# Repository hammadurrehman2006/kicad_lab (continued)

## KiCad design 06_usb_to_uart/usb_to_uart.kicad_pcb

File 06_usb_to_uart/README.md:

# Day 5 – USB to UART Converter (CP2102)

This is **Day 5** of my **10-Day PCB Design Challenge**.
After getting delayed due to heavy rain 🌧️ on 19th Aug, I’m back with my next project – a **USB to UART Converter PCB** designed using **KiCad**.

This project is special because it’s my **first SMD-based PCB design** 🎉 and also introduces **vias** and **ESD protection** for improved reliability.

---

## 📜 Project Overview

The circuit is based on the **CP2102 USB-to-UART Bridge Controller**, which enables easy communication between a computer’s USB port and microcontrollers or other UART-based devices.

### Key Features:

* **USB Type-C input**
* **CP2102 IC (SMD package)**
* **ESD protection diodes** → *LESD5D5.0CT1G*
* **LED indicators** for Power, TX, and RX
* **Decoupling capacitors** for noise reduction
* **External pins** (VCC, GND, TX, RX, RST) for easy interfacing
* **Vias** for better routing on the 2-layer PCB

---

## 🛠 Tools Used

* **KiCad** → Schematic & PCB Design
* **GitHub** → Version control & documentation

---

## 📂 Files in This Project

* **Schematic & PCB files** (KiCad project)
* **Gerber files** (for fabrication)
* **Drill files**
* **Images** (schematic, PCB layout, 3D preview)

---

## 📸 Project Images

### Schematic

### PCB Layout

### 3D PCB Preview

### 3D PCB without components Preview

---

## 📬 Repository Info

* **Folder Name:** `06_usb_to_uart`
* **Author:** Muhammad Hammad ur Rehman
* **License:** Open for learning & educational purposes

---

⚡ This project marks a milestone for me as I move from **through-hole designs** to **SMD-based PCBs** while also learning to use **vias** and **protection circuits** in real-world designs.

---

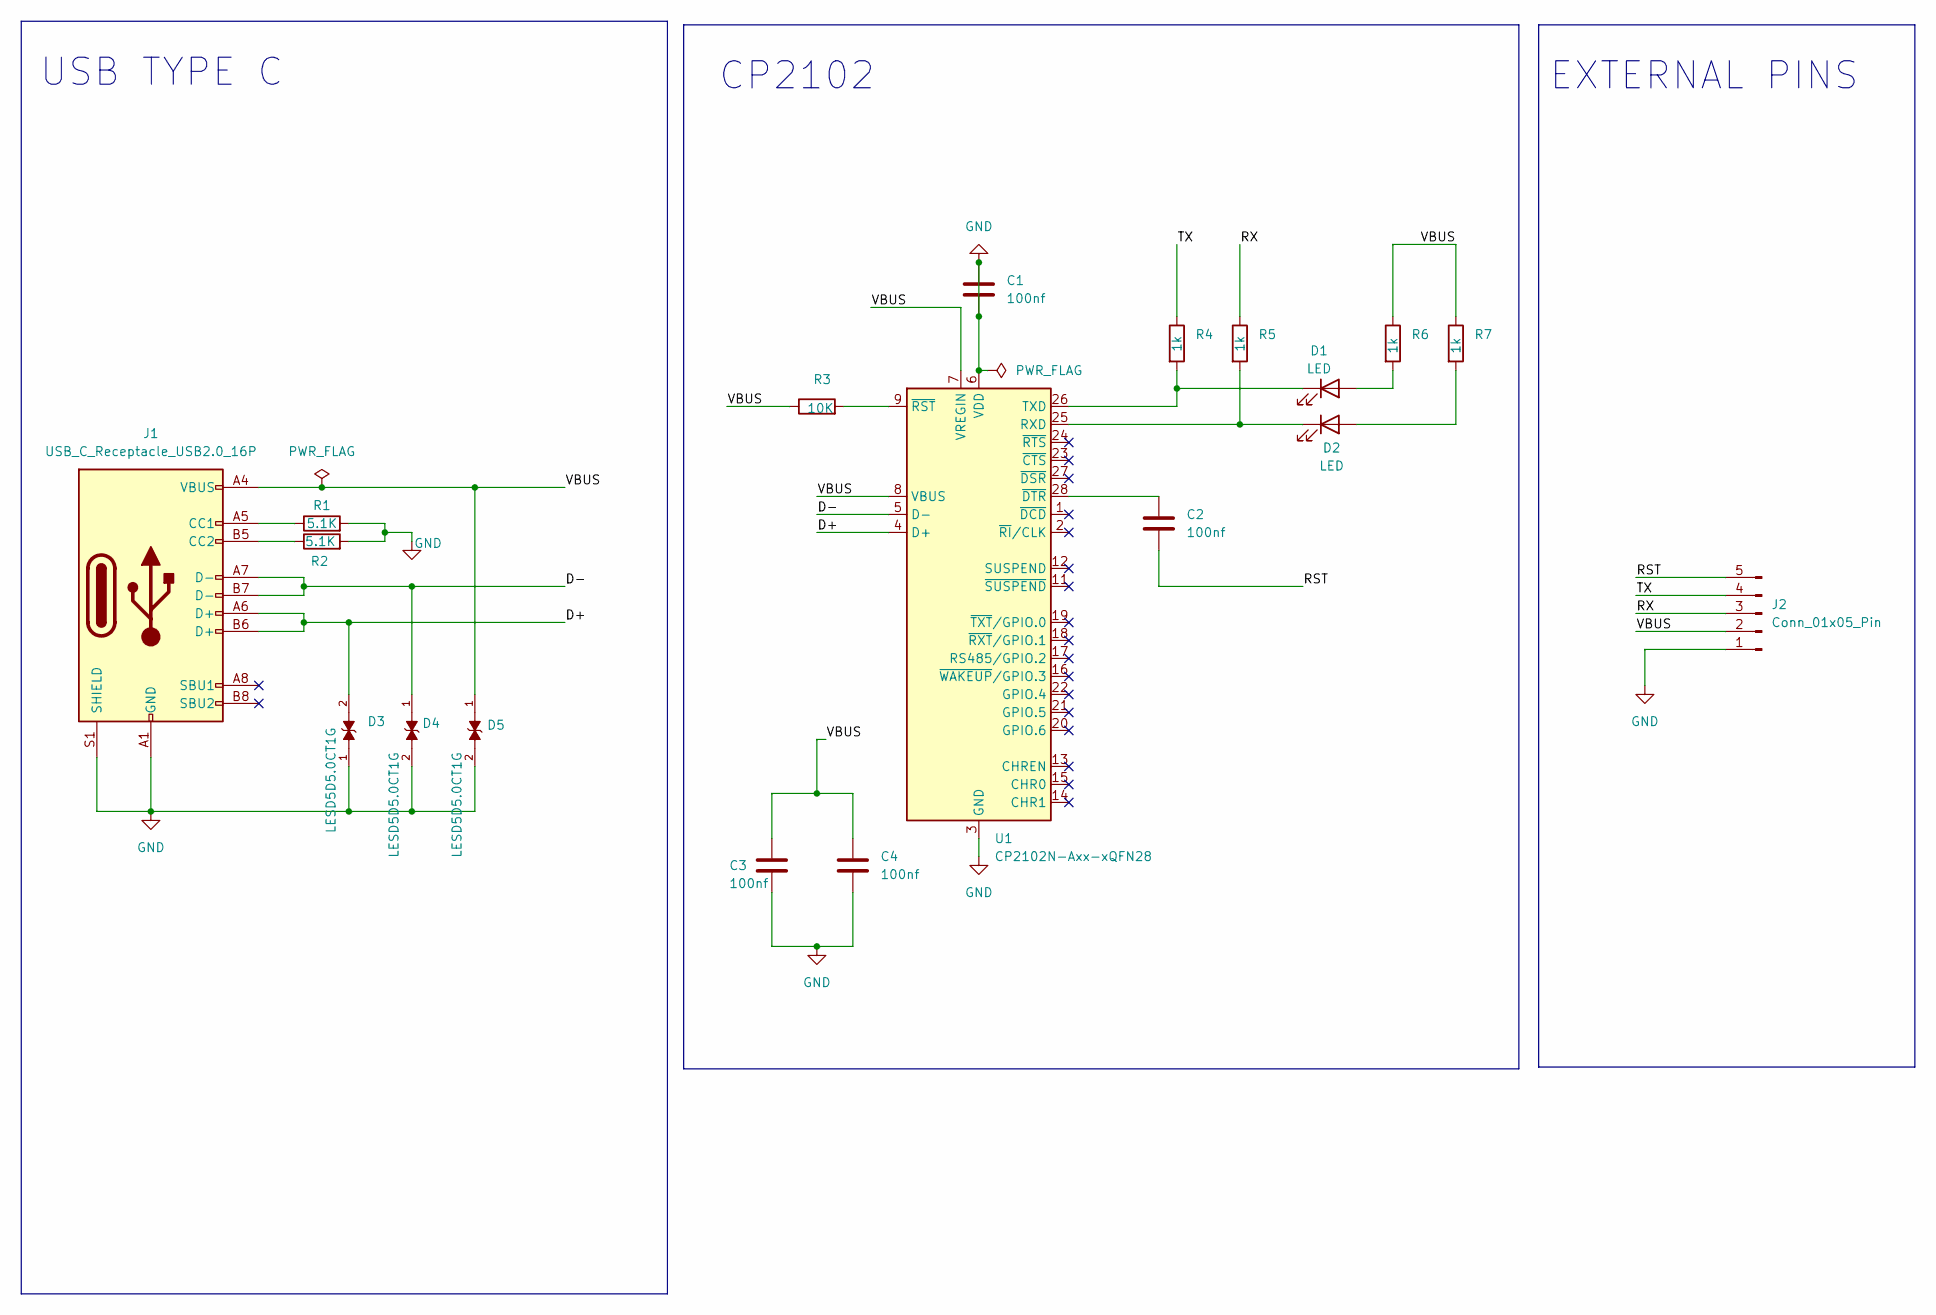
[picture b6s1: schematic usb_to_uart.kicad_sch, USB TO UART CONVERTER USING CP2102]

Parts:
C1, C2, C3, C4: 100nf; C_0201_0603Metric
D1, D2: LED; LED_0201_0603Metric
D3, D4, D5: LESD5D5.0CT1G; TVS_LESD5D5.0CT1G; PARTREV O
J1: USB_C_Receptacle_USB2.0_16P; USB_C_Receptacle_HRO_TYPE-C-31-M-12
J2: Conn_01x05_Pin; PinHeader_1x05_P2.54mm_Horizontal
R1, R2: 5.1K; R_0201_0603Metric
R3: 10K; R_0201_0603Metric
R4, R5, R6, R7: 1k; R_0201_0603Metric
U1: CP2102N-Axx-xQFN28; QFN-28-1EP_5x5mm_P0.5mm_EP3.35x3.35mm

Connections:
/D+: D3.2, J1.A6 (D+), J1.B6 (D+), U1.4 (D+)
/D-: D4.1, J1.A7 (D-), J1.B7 (D-), U1.5 (D-)
/RST: C2.2, J2.5
/RX: J2.3, R5.1
/TX: J2.4, R4.1
/VBUS: C3.1, C4.1, D5.1, J1.A4 (VBUS), J1.A9 (VBUS), J1.B4 (VBUS), J1.B9 (VBUS), J2.2, R3.1, R6.1, R7.1, U1.7 (VREGIN), U1.8 (VBUS)
GND: C1.1, C1.2, C3.2, C4.2, D3.1, D4.2, D5.2, J1.A1 (GND), J1.A12 (GND), J1.B1 (GND), J1.B12 (GND), J1.S1 (SHIELD), J2.1, R1.2, R2.2, U1.3 (GND), U1.6 (VDD), U1.29 (GND)
unnamed: D1.2 (A), R6.2
unnamed: D1.1 (K), R4.2, U1.26 (TXD)
unnamed: D2.2 (A), R7.2
unnamed: D2.1 (K), R5.2, U1.25 (RXD)
unnamed: J1.A5 (CC1), R1.1
unnamed: J1.B5 (CC2), R2.1
unnamed: C2.1, U1.28 (~DTR)
unnamed: R3.2, U1.9 (~RST)

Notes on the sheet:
CP2102
USB TYPE C
EXTERNAL PINS

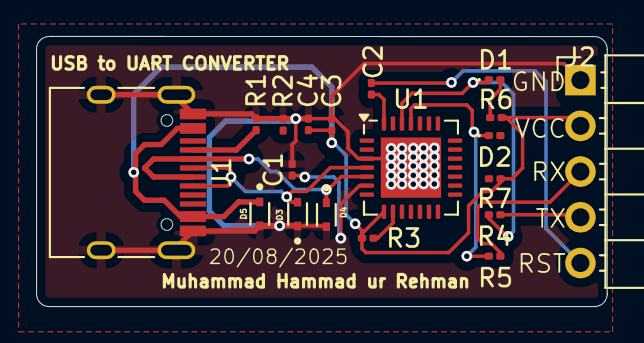
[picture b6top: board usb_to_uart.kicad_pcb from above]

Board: 2 copper layers, 31.7 x 15.0 mm, 19 parts (0 on the bottom side), 15 nets.

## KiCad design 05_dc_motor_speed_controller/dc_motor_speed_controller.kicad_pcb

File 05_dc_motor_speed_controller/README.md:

# Day 4 – DC Motor Speed Controller (PCB Design)

This is **Day 4** of my **10-Day PCB Design Challenge**.  
For today’s project, I designed a **DC Motor Speed Controller PCB** using **KiCad**.  
The circuit is based on a **555 Timer IC** in astable mode, generating PWM to control motor speed via a transistor.

---

## 📜 Project Overview
The circuit includes:
- **1 × Potentiometer** (for speed adjustment)  
- **1 × 555 Timer IC**  
- **2 × Capacitors**  
- **3 × Resistors**  
- **1 × Power Transistor (Q1)**  
- **3 × Diodes**  
- **1 × LED** (status indicator)  
- **2 × 2-Pin Screw Terminals** (power in, motor out)

---

## 🛠 Tools Used
- **KiCad** for schematic and PCB layout  
- **GitHub** for version control  

---

## 📂 Files in This Project
- **Schematic & PCB files** (KiCad project)  
- **Gerber files** for fabrication  
- **Drill files** (included inside Gerbers folder)  
- **Images** for quick preview in this README  

---

## 📸 Project Images

### Schematic

### PCB Layout

### PCB with Components

### PCB Board

---

## 📬 Repository Info
- **Folder Name:** `05_dc_motor_speed_controller`  
- **Author:** Muhammad Hammad ur Rehman  
- **License:** Open for learning and educational purposes  

---

## 🔗 Connect with Me
[LinkedIn](https://www.linkedin.com/in/mhammadurrehman) • [GitHub](https://github.com/hammadurrehman2006)

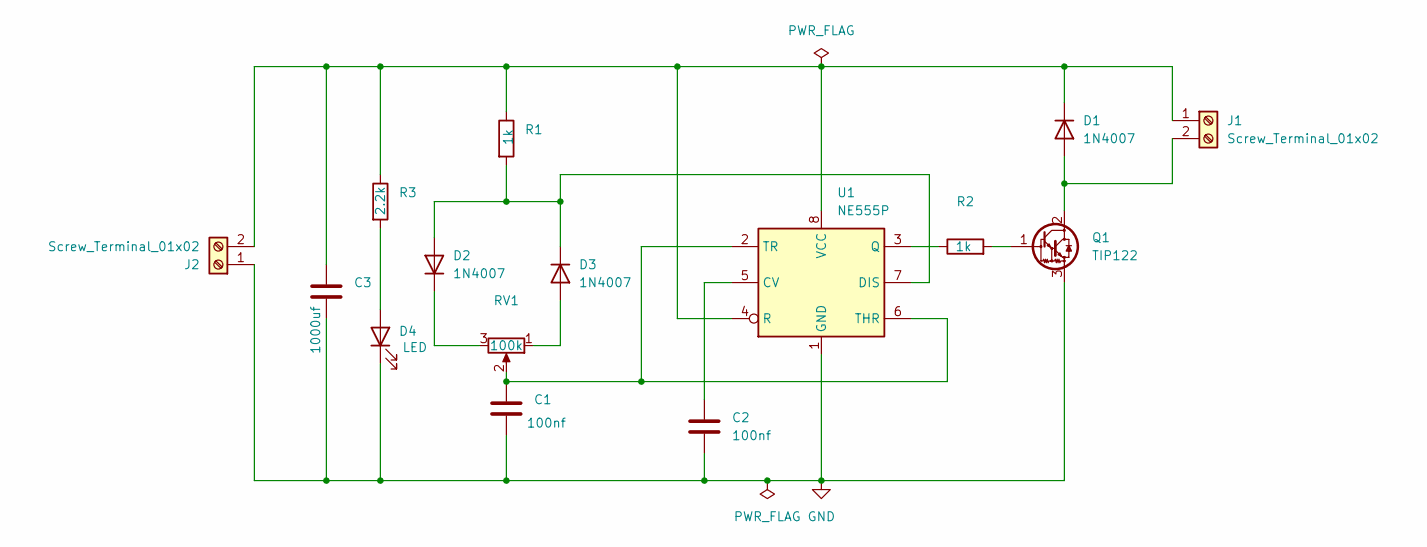
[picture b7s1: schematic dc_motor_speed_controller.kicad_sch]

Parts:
C1, C2: 100nf; C_Disc_D4.7mm_W2.5mm_P5.00mm
C3: 1000uf; CP_Radial_D10.0mm_P5.00mm
D1, D2, D3: 1N4007; D_DO-41_SOD81_P10.16mm_Horizontal
D4: LED; LED_D5.0mm
J1, J2: Screw_Terminal_01x02; TerminalBlock_bornier-2_P5.08mm
Q1: TIP122; TO-220-3_Vertical
R1, R2: 1k; R_Axial_DIN0204_L3.6mm_D1.6mm_P7.62mm_Horizontal
R3: 2.2k; R_Axial_DIN0204_L3.6mm_D1.6mm_P7.62mm_Horizontal
RV1: 100k; Potentiometer_Alps_RK163_Single_Horizontal
U1: NE555P; DIP-8_W7.62mm

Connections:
GND: C1.2, C2.2, C3.2, D4.1 (K), J2.1, Q1.3 (E), U1.1 (GND)
unnamed: D1.2 (A), J1.2, Q1.2 (C)
unnamed: C3.1, D1.1 (K), J1.1, J2.2, R1.1, R3.1, U1.4 (R), U1.8 (VCC)
unnamed: D2.2 (A), D3.1 (K), R1.2, U1.7 (DIS)
unnamed: D2.1 (K), RV1.3
unnamed: D3.2 (A), RV1.1
unnamed: D4.2 (A), R3.2
unnamed: Q1.1 (B), R2.2
unnamed: C2.1, U1.5 (CV)
unnamed: R2.1, U1.3 (Q)
unnamed: C1.1, RV1.2, U1.2 (TR), U1.6 (THR)

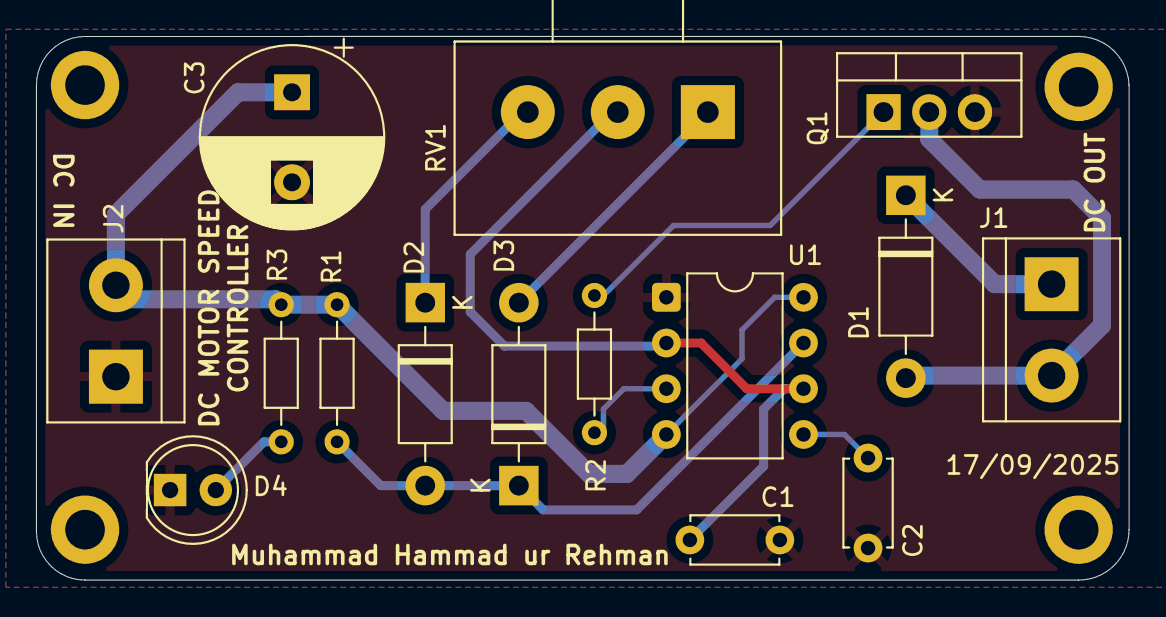
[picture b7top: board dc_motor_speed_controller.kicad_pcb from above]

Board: 2 copper layers, 60.7 x 30.2 mm, 15 parts (0 on the bottom side), 11 nets.

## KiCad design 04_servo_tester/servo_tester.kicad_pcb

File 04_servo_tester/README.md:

# Day 3 – Servo Tester (PCB Design)

This is **Day 3** of my **10-Day PCB Design Challenge**, where I design PCB projects starting from simple circuits and gradually moving towards more complex ones.

For today’s design, I created a **2-layer Servo Tester PCB** using **KiCad**.  
This circuit is based on a **555 Timer IC** and a potentiometer to generate PWM signals for testing servo motors.

---

## 📜 Project Overview
The circuit includes:
- **1 × Potentiometer**  
- **1 × 555 Timer IC**  
- **1 × Capacitor**  
- **3 × Resistors**  
- **1 × Diode**  
- **1 × LED**  
- **1 × 2-Pin Connector**  
- **1 × 3-Pin Connector**  

---

## 🛠 Tools Used
- **KiCad** for schematic and PCB layout  
- **GitHub** for version control  

---

## 📂 Files in This Project
- **`schematic.png`** – Circuit schematic  
- **`board.png`** – PCB front view  
- **`boardC.png`** – PCB with components  
- **`layout.png`** – PCB layout view  

---

## 📸 Project Images

### Schematic

### PCB Board

### PCB with Components

### Layout

---

## 📅 Challenge Context
This project is part of my **10-Day PCB Design Challenge**:
- **Day 1:** AC to DC Converter (Single Layer PCB)  
- **Day 2:** Transformerless Power Supply (2-Layer PCB)  
- **Day 3:** Servo Tester (2-Layer PCB with 555 Timer)  

---

## 📬 Repository Info
- **Folder Name:** `04_servo_tester`  
- **Author:** Muhammad Hammad ur Rehman  
- **License:** Open for learning and educational purposes  

---

## 🔗 Connect with Me
[LinkedIn](https://www.linkedin.com/in/mhammadurrehman) • [GitHub](https://github.com/hammadurrehman2006)

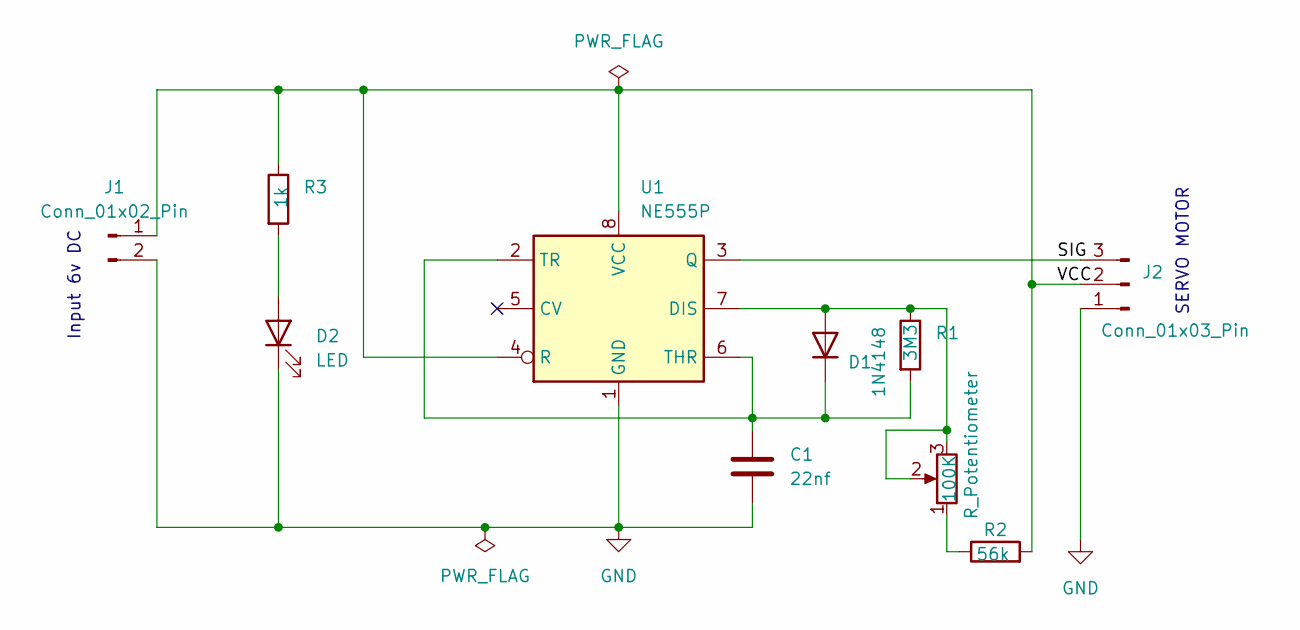
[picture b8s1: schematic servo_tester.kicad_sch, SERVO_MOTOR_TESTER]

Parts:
100K: R_Potentiometer; Potentiometer_Alps_RK163_Single_Horizontal
C1: 22nf; C_Disc_D4.3mm_W1.9mm_P5.00mm
D1: 1N4148; D_DO-35_SOD27_P7.62mm_Horizontal
D2: LED; LED_D3.0mm
J1: Conn_01x02_Pin; PinHeader_1x02_P2.54mm_Horizontal
J2: Conn_01x03_Pin; PinHeader_1x03_P2.54mm_Horizontal
R1: 3M3; R_Axial_DIN0204_L3.6mm_D1.6mm_P7.62mm_Horizontal
R2: 56k; R_Axial_DIN0204_L3.6mm_D1.6mm_P7.62mm_Horizontal
R3: 1k; R_Axial_DIN0204_L3.6mm_D1.6mm_P7.62mm_Horizontal
U1: NE555P; DIP-8_W7.62mm

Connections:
/SIG: J2.3, U1.3 (Q)
/VCC: J1.1, J2.2, R2.2, R3.1, U1.4 (R), U1.8 (VCC)
GND: C1.2, D2.1 (K), J1.2, J2.1, U1.1 (GND)
unnamed: 100K.1, R2.1
unnamed: 100K.2, 100K.3, D1.2 (A), R1.1, U1.7 (DIS)
unnamed: C1.1, D1.1 (K), R1.2, U1.2 (TR), U1.6 (THR)
unnamed: D2.2 (A), R3.2

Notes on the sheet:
SERVO MOTOR
Input 6v DC

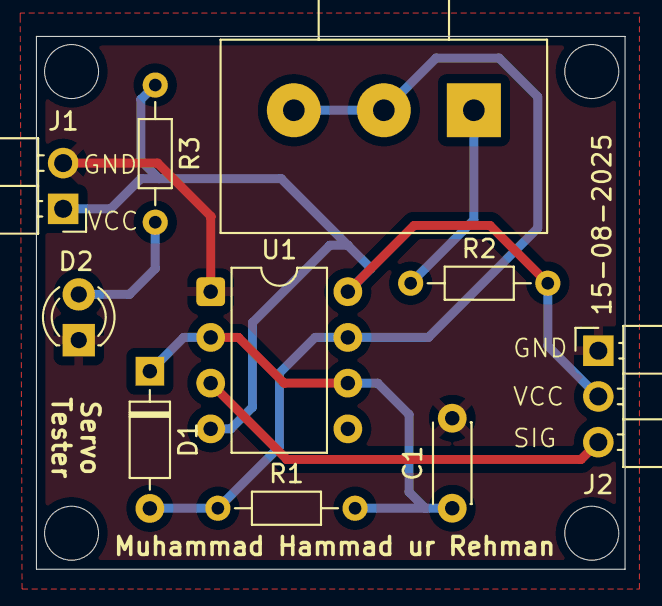
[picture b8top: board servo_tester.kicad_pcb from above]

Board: 2 copper layers, 32.7 x 29.6 mm, 10 parts (0 on the bottom side), 7 nets.

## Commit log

2025-08-05 Create 01_sp02_monitor
2025-08-14 Created 02_ac-to_dc_converter
2025-08-16 README.md Added
2025-08-16 03_transformerless_power_supply Created
2025-08-17 04_servo_tester Created
2025-08-17 Images and README Added
2025-08-18 GND Zone Updated
2025-08-18 05_dc_motor_speed_controller Created
2025-08-18 Images Added
2025-08-21 Created 06_usb_to_uart
2025-08-22 Created 07_dc_boost_converter
2025-08-23 Created 08_motor_driver_with_DRV8833
2025-08-23 3d_models Added
    External 3d models downloaded from other resources.
2025-08-23 Libraries Added
    External Libraries that are not included in KiCad 9.0
2025-11-09 Add home_automation_using_esp32
2025-11-09 Add Stm32_gps_tracker
2025-11-09 Add 3d models
2025-11-09 Add Sine_wave_inverter
2025-11-09 Add libraries
